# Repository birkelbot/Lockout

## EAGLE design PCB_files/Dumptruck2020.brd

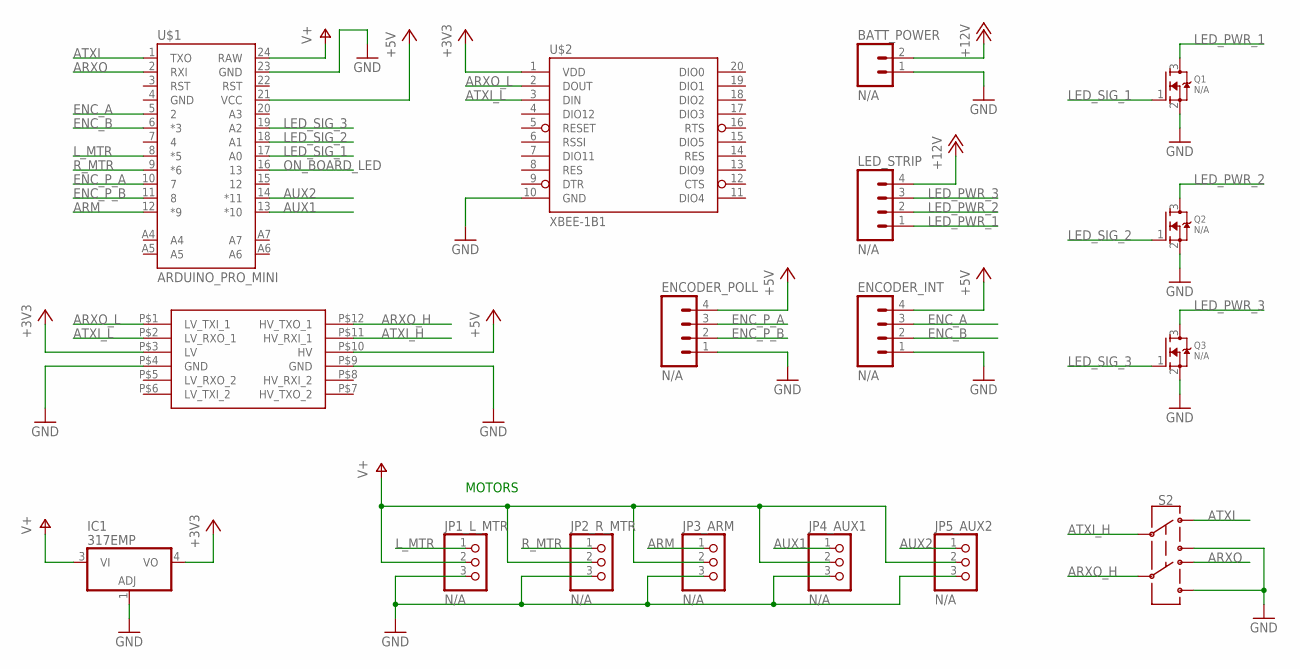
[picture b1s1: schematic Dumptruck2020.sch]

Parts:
BATT_POWER: N/A; 1X02
ENCODER_INT: N/A; 1X04_LOCK
ENCODER_POLL: N/A; 1X04_LOCK
IC1: 317EMP; SOT223
JP1_L_MTR, JP2_R_MTR, JP3_ARM, JP4_AUX1, JP5_AUX2: N/A; 1X03
LED_STRIP: N/A; 1X04_LOCK
Q1, Q2, Q3: N/A; SOT23
S2: SWITCH-DPDT-SMD-AYZ0202; SWITCH_DPDT_SMD_AYZ0202
U$1: ARDUINO_PRO_MINI
U$2: XBEE-1B1; XBEE-1
U$3: LOGIC_LEVEL_CONVERTER

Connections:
+3V3: IC1.4 (VO), U$2.1 (VDD), U$3.P$3 (LV)
+5V: ENCODER_INT.4, ENCODER_POLL.4, U$1.21 (VCC), U$3.P$10 (HV)
+12V: BATT_POWER.2, LED_STRIP.4
ARM: JP3_ARM.1, U$1.12 (*9)
ARXO: S2.4, U$1.2 (RXI)
ARXO_H: S2.5, U$3.P$12 (HV_TXO_1)
ARXO_L: U$2.2 (DOUT), U$3.P$1 (LV_TXI_1)
ATXI: S2.1, U$1.1 (TXO)
ATXI_H: S2.2, U$3.P$11 (HV_RXI_1)
ATXI_L: U$2.3 (DIN), U$3.P$2 (LV_RXO_1)
AUX1: JP4_AUX1.1, U$1.13 (*10)
AUX2: JP5_AUX2.1, U$1.14 (*11)
ENC_A: ENCODER_INT.3, U$1.5 (2)
ENC_B: ENCODER_INT.2, U$1.6 (*3)
ENC_P_A: ENCODER_POLL.3, U$1.10 (7)
ENC_P_B: ENCODER_POLL.2, U$1.11 (8)
GND: BATT_POWER.1, ENCODER_INT.1, ENCODER_POLL.1, IC1.1 (ADJ), JP1_L_MTR.3, JP2_R_MTR.3, JP3_ARM.3, JP4_AUX1.3, JP5_AUX2.3, Q1.2 (S), Q2.2 (S), Q3.2 (S), S2.3, S2.6, U$1.23 (GND), U$2.10 (GND), U$3.P$4 (GND), U$3.P$9 (GND)
LED_PWR_1: LED_STRIP.1, Q1.3 (D)
LED_PWR_2: LED_STRIP.2, Q2.3 (D)
LED_PWR_3: LED_STRIP.3, Q3.3 (D)
LED_SIG_1: Q1.1 (G), U$1.17 (A0)
LED_SIG_2: Q2.1 (G), U$1.18 (A1)
LED_SIG_3: Q3.1 (G), U$1.19 (A2)
L_MTR: JP1_L_MTR.1, U$1.8 (*5)
ON_BOARD_LED: U$1.16 (13)
R_MTR: JP2_R_MTR.1, U$1.9 (*6)
V+: IC1.3 (VI), JP1_L_MTR.2, JP2_R_MTR.2, JP3_ARM.2, JP4_AUX1.2, JP5_AUX2.2, U$1.24 (RAW)

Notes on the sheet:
MOTORS

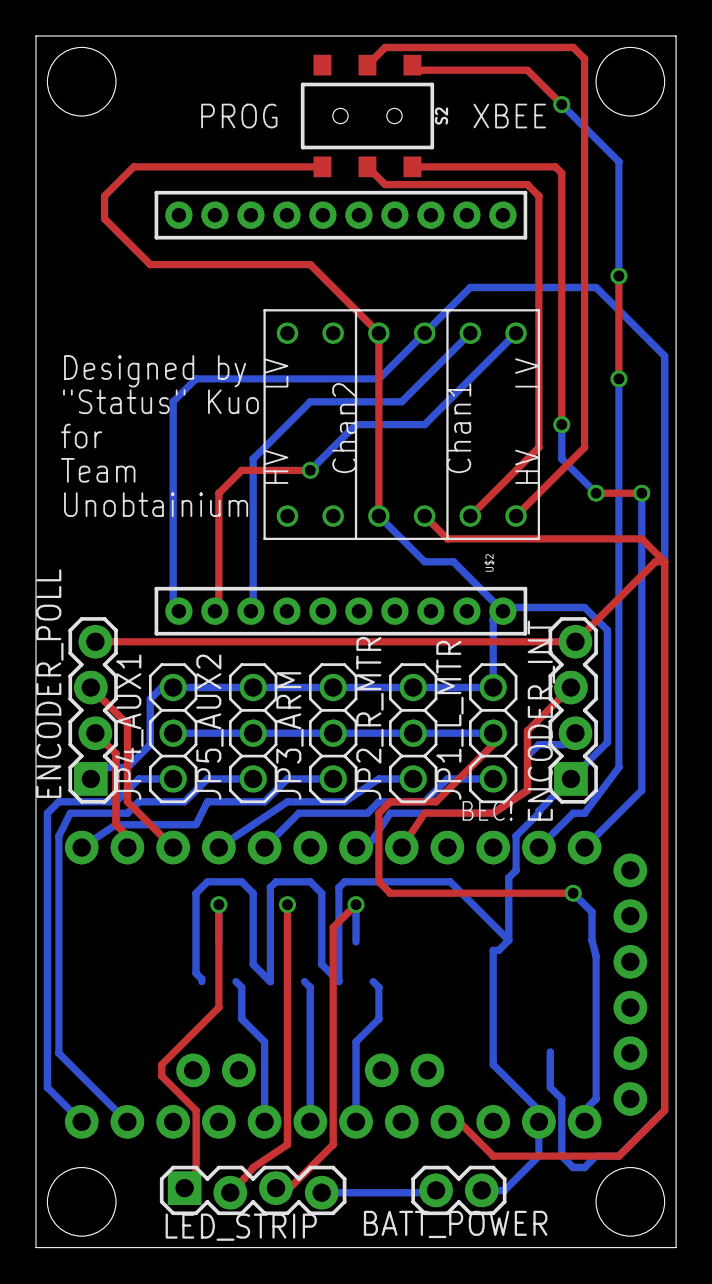
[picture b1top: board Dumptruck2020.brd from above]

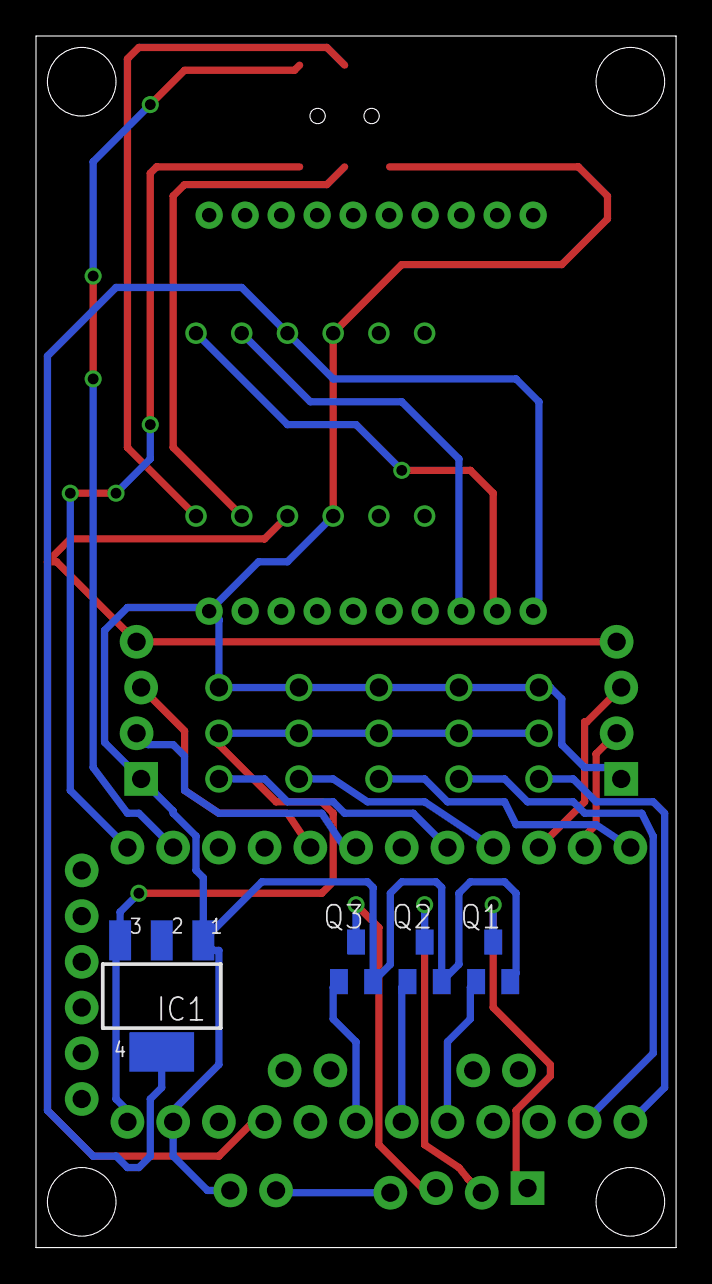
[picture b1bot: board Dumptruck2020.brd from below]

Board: 2 copper layers, 35.6 x 67.3 mm, 17 parts (4 on the bottom side), 26 nets.

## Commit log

2020-02-06 First commit. Forking from https://github.com/birkelbot/Wall-F_2019.git
2020-02-06 Removed all the PID-related logic. After testing using PID in the 2019 season, I decided it wasn't useful/reliable enough to continue using it. The new version of the robot does not have an encoder, 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
2020-02-21 Adding 2020 New PCB Files
    This commit adds the new 2020 Eagle files for the
    "Controls" board. Features a new switch.
2020-02-22 Updates to make it work with Python 3. Also updated the local test to be enabled/disabled using a macro rather than having to comment out huge blocks of Arduino code. Also some minor tunings to the d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
2020-05-30 Tweaks to make code work on new bot.
2021-10-06 Added basic pygame UI to allow use of Bluetooth controllers. Pygame will only process bluetooth controllers when the game is the 'active' window, and there was previosly no game window rendered for t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
2022-02-12 Small tunings
2022-02-17 Added forward declarations of functions in Arduino code
2022-02-17 Added ability to use bumpers as a way to slowly move the arm up/down at a fixed command -- good for lowering the arm back to the ground in a more controlled manner
2022-02-17 Fix a bug with the scale factor calculation in arcadeDrive
2023-02-15 Tuning
2023-02-15 Added ability for using dual analog trigger input for arm control
2023-02-15 Added initialization for dual analog triggers for arm control
2023-02-15 Debugging getArmRawFromDualAnalog and fixing channel numbers for running on RPi
2023-02-15 Added a button listener script for running the driver station by pushing the button on the Pi Case 40
2023-02-15 Added a bash launcher script for ButtonListener.py
2023-03-30 Set up right bumper as an 'arm turbo' button, and set the default arm commands to be lower power. Also updated the drive to be more sensitive now that I have the tall joysticks installed on the Xbox 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
2023-03-30 Accidentally removed the yNeg and rNeg from the arcadeDrive's calculation of motor commends. Restoring.
2023-03-30 Removed a debugging print line
2023-09-24 Adding config for VS Code
2024-12-15 Tweaks made directly on driver station RPi at competitions from 2022
2025-04-03 Un-inverting the left joystick for drive. I'm using the old PCB, and for some reason it's different than what was previously working for the new PCB, not sure why.
2025-04-03 Adding a tunable turning correction to help the robot drive straight
2025-04-03 Re-inverting the L joystick for drive (I realized I had the PWM wires flip-flopped on the old PCB, which is why it was backwards before); also un-invert the R drive motor (I realized that the ESCs do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
2025-04-03 Rename HelloWorld to remove the redundant '.ino'
2025-04-05 Re-introducing the 'arm up slow' button on the right bumper, and moving 'arm turbo' to the 'A' button. I want 'arm up slow' so that I can get over the lifted floor panels more easily.
2025-05-25 Moving HelloWorld.ino into its own subfolder because the Arduino IDE is opening all .ino files in the same directory and trying to compile them together as one sketch. This obviously breaks because I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

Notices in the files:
parts and their libraries:
SparkFun-Boards: Licensing: Creative Commons ShareAlike 4.0 International - https://creativecommons.org/licenses/by-sa/4.0
